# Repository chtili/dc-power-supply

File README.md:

# dc-power-supply

A linear AC to DC converter based on a power supply built in my Circuits I class. I converted our design into a PCB, optimizing for high current demand. 

## Contents

- `linear-power-supply-board/` — KiCad project (schematic + PCB layout)
  - `gerbers/` — fabrication outputs (Gerbers + drill files)

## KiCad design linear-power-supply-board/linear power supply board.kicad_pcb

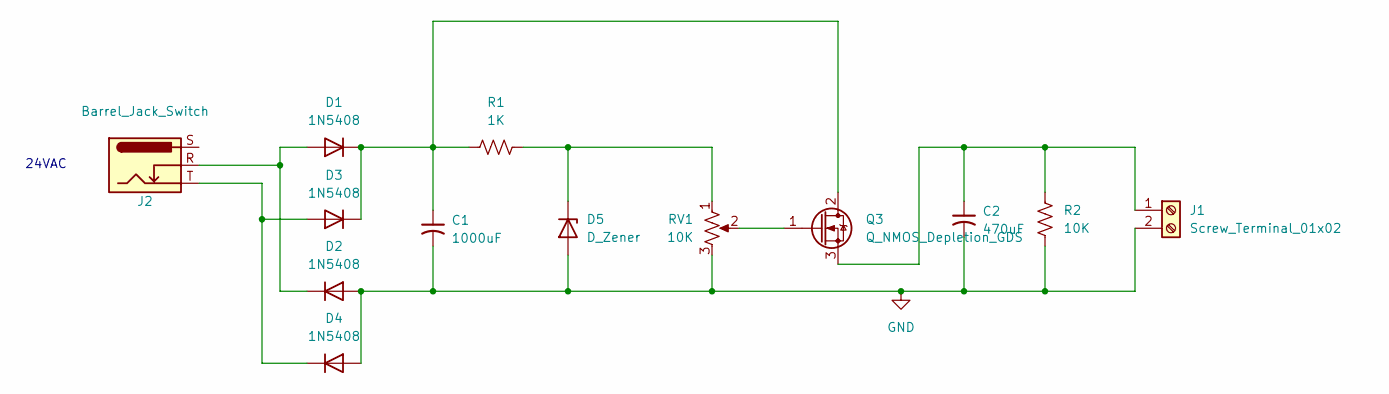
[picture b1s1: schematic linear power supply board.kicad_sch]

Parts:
C1: 1000uF; CP_Radial_D12.5mm_P5.00mm
C2: 470uF; CP_Radial_D10.0mm_P5.00mm
D1, D2, D3, D4: 1N5408; D_DO-201AD_P15.24mm_Horizontal
D5: D_Zener; D_DO-41_SOD81_P7.62mm_Horizontal
J1: Screw_Terminal_01x02; TerminalBlock_CUI_TB007-508-02_1x02_P5.08mm_Horizontal
J2: Barrel_Jack_Switch; Jack_3.5mm_CUI_SJ1-3523N_Horizontal; MFR P/N SJ1-3524N
Q3: Q_NMOS_Depletion_GDS; TO-220-3_Vertical; MFR P/N IRF530A
R1: 1K; R_Axial_DIN0207_L6.3mm_D2.5mm_P7.62mm_Horizontal
R2: 10K; R_Axial_DIN0207_L6.3mm_D2.5mm_P7.62mm_Horizontal
RV1: 10K; TRIM_3362P-1-203

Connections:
GND: C1.2, C2.2, D2.2 (A), D4.2 (A), D5.2 (A), J1.2, R2.2, RV1.3
unnamed: D1.2 (A), D2.1 (K), J2.R
unnamed: C1.1, D1.1 (K), D3.1 (K), Q3.2 (D), R1.2
unnamed: D3.2 (A), D4.1 (K), J2.T
unnamed: D5.1 (K), R1.1, RV1.1
unnamed: C2.1, J1.1, Q3.3 (S), R2.1
unnamed: Q3.1 (G), RV1.2

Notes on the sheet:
24VAC

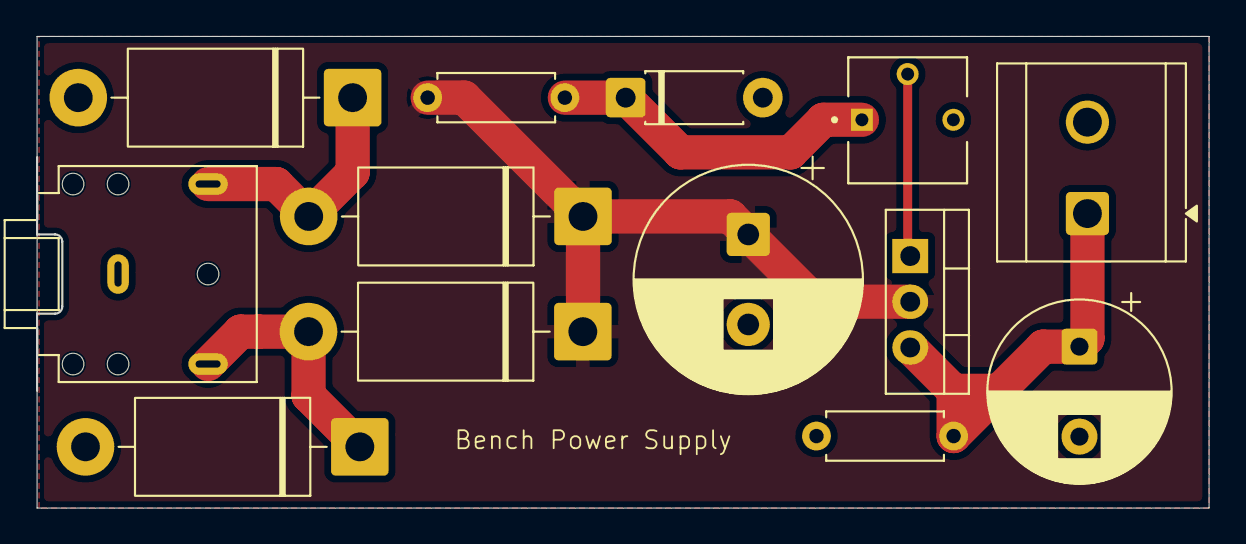
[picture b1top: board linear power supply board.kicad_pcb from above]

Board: 2 copper layers, 65.1 x 26.1 mm, 13 parts (0 on the bottom side), 7 nets.
